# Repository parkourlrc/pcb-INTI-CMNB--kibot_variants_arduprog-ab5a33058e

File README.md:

# KiBot variants example

This is an example of how to use variants with [KiBot](https://github.com/INTI-CMNB/KiBot).

> [!TIP]
> They can be migrated to native KiCad 10 variants, here is an [example](https://inti-cmnb.github.io/kibot_variants_arduprog_native/)

## Index

* [Definition](#Definition)
* [Implementation](#Implementation)
* [Example](#Example)
* [**Results**](#Results)
  * [Schematic PDF](#Schematic-PDF)
  * [Bill of Materials](#Bill-of-Materials)
  * [PCB PDF](#PCB-PDF)
  * [Gerbers](#Gerbers)
  * [Position](#Position)
  * [3D Model](#3D-Model)
* [Changing values](#Changing-values)
* [A complete example](#A-complete-example)

# Definition

In the KiBot context a variant is what is usually known as an *assembly variant*.
So the idea is that you have **one** PCB, but various different *variants* (*flavors*) of the product.
The difference between them is which components are used.

Typical applications are:
- Optional functionality
- Support for different normatives
- Testing purposes

Currently KiBot can handle not only which components are soldered, but also different values.
The support for different values is complex and only used by a minority.
So please be patient if some use case isn't well covered, just report it.

# Implementation

To create a variant you must add specific fields to the components in the schematic.
Currently KiBot supports three methodes:

- **KiBoM style**: one field, usually named *Config*, contains information to include or exclude a component for one or more variants.
- **KiCost style**: one field assigns the component to one or more groups, you provide a regular expression to include certain groups.
- **IBoM style**: one field assigns the component to a group, you provide lists to exclude or include certain groups.

# Example

The best way to explain how to use it is using an example.
We start with an hypothetic design: the *programmer* section of the [Arduino UNO R3](https://content.arduino.cc/assets/UNO-TH_Rev3e_sch.pdf).
The schematic is the following:

This is basically an ATMega8U2 used as a bridge between USB and the Arduino UNO serial port.
So we will assume this board is useful. We'll also assume we have three possible uses:

- The full board with USB support. We'll name it **USB** variant.
- A version of the board that we want to use as a plain microcontroller. So we remove the USB. We'll name it **XTAL** variant.
- An even more modest version where we use the internal clock oscillator and we can remove the crystal. We'll name it **default** variant.

Additionally:

- In the USB version we want to remove the ICSP1 connector. We'll flash the CPU in-house and the user won't need to do it. ICPS1 will be solded for the other two variants.
- The J4 connector is completely optional. It won't be included in any variant.

The first step is to choose a variant mechanism. For this example we will use the [KiBoM](https://github.com/SchrodingersGat/KiBoM) style.
This style puts more information inside the schematic, so you need to provide less information from outside.

Now that we chose a format we must add the corresponding *tags*. We can identify four groups of components here:

- The USB components (J2, F1, R1, R2, RV1, RV2 and FB1). Used only for the **USB** variant.
- The ICSP1 connector (J5). Excluded from the **USB** variant.
- The crystal components (R3, Y1, C3, C4). Used only for the **USB** and **XTAL** variants.
- The 2x2M connector (J4). Never used.

To mark components that will be added to the board only for certain variant KiBoM uses **+VARIANT**.
And when we want to exclude a component from a variant we use **-VARIANT**.

We'll use the default *Config* field. So lets see what we'll use for each group.

- For the USB components we'll use **+USB** because these components will be used only for the **USB** variant.
- For the ICSP1 connector we'll use **-USB** because this component will be solded for all variants, except **USB**.
- Now the crystal stuff is a little bit more complex. We could use **+XTAL**, but then these components won't be included in the **USB** version.
  So what we use is **+USB,+XTAL** this makes the components available for both variants.
- The J4 case is handled in a different way. KiBoM filters removes any component mentioning the **DNF** word in the config. So we can just use it.

Now that we know what to use we'll add the *Config* field to the mentioned components.
To make it faster we can add it to one component, lets say to J4, and then use the *Tools -> Edit symbol fields* menu option.
Here is what we should have in the *Config* field:

This is all we need to add to the schematic. Now is time to configure KiBot.

If you don't know about the KiBot file format you could be interested in reading the following [explanation](https://github.com/INTI-CMNB/KiBot/blob/master/docs/KiPlotYAML.md).
YAML files are self explanatory, so perhaps you can go on even without knowing about the format.

Ok, now we have to define the three variants we mentioned before: **USB**, **XTAL** and **default**.
All variants will be put in a section named **variants**. So we'll create a list of items, each item is a variant definition.
Lets start with the simplest: **default**. Here is what we use:

```yaml
variants:
  - name: 'default'
    comment: 'Minimal PCB no USB'
    type: kibom
```

This is the section **variants** and its first item. The name is **default** and we added a comment to remmember what this variant is.
We also define the type as **kibom**, what we called *style*.

Now lets go for the second, here we add:

```yaml
  - name: 'USB'
    comment: 'Full board'
    type: kibom
    file_id: _USB
    variant: USB
```

You'll notice two new attributes: `file_id` and `variant`. The first is what we'll add to the names of the files in order to distinguish from the **default**.
And the second ... well this is just the *tag* we used to mark **USB** components.

You should be able to figure out how to define the third variant, here we go:

```yaml
  - name: 'XTAL'
    comment: 'No USB, but crystal included'
    type: kibom
    file_id: _XTAL
    variant: XTAL
```

A little bit long, but simple. Here is all together:

```yaml
variants:
  - name: 'default'
    comment: 'Minimal PCB no USB'
    type: kibom

  - name: 'USB'
    comment: 'Full board'
    type: kibom
    file_id: _USB
    variant: USB

  - name: 'XTAL'
    comment: 'No USB, but crystal included'
    type: kibom
    file_id: _XTAL
    variant: XTAL
```

This is all we need to define the variants. Of course our config file must define what to do with the variants.
But this document is about the variants, we won't focuse on the rest.
You can see the whole configuration file [here](ardu_prog.kibot.yaml).

What now? How can we tell KiBot what variant to use?
There are three methodes:

1. Use the `variant` option for an specific output.
2. Select a default variant to be used by all outputs that doesn't specify a variant.
3. Same as above but from the command line.

The simplest way is the third. In this case we just need to add `-g variant=NAME` to the command line.
Lets say we have a copy of the repo containing this example and we want to generate the BoM.
In our example the HTML BoM output is named `bom_html` so we can just run:

```bash
kibot -s run_erc,run_drc -d Result bom_html
```

This will create `Result/BoM/t1-bom.html`. To generate the BoM for the **USB** variant we can use:

```bash
kibot -s run_erc,run_drc -d USB -g variant=USB bom_html
```

And we'll get a different BoM in `USB/BoM/t1-bom_USB.html`.

The CI/CD workflow for this repo runs the ERC and DRC checks and then generates all the configured outputs for the three variants.
The commands used are approximately these:

```bash
kibot -d Generated -s run_drc -i
kibot -d Generated -s run_erc -i
kibot -d Generated/default -g variant=default -s run_erc,run_drc
kibot -d Generated/USB -g variant=USB -s run_erc,run_drc
kibot -d Generated/XTAL -g variant=XTAL -s run_erc,run_drc
```

The first two are the checks, no output generated. The other three skips the checks and generates all outputs for each variant.
All files are stored in the `Generated` folder.

# Results

Here is what we get, you can download the results obtained on GitHub CI/CD Actions from [here](https://github.com/INTI-CMNB/kibot_variants_arduprog/actions/runs/4584580459).
Click on the images to get a larger image or the generated document.

## Schematic PDF

Excluded components are marked with a cross:

- Default variant

- XTAL variant

- USB variant

## Bill of Materials

Excluded components are listed as DNF in a separated list. Note we could also remove them.

- Default variant

- XTAL variant

- USB variant

The XLSX files contain the same information, arranged a little bit different, here is the USB variant:

## PCB PDF

Excluded components are marked with a cross in the *.Fab layer. Their solder paste and adhesive glue is removed from *.Paste and *.Adhes.
The following PDFs were gnerated including F.Fab, F.Paste, F.Adhes and Dwgs.User:

- Default variant

- XTAL variant

- USB variant

## Gerbers

Excluded components are marked with a cross in the *.Fab layer. Their solder paste and adhesive glue is removed from *.Paste and *.Adhes:

- Default variant

- XTAL variant

- USB variant

## Position

Here only the fitted components are included in the pick and place file:

- Default variant
```
### Module positions - created on Thu 10 Sep 2020 20:10:57  ###
### Printed by KiBot
## Unit = mm, Angle = deg.
## Side : both
# Ref   Val                  Package                                     PosX       PosY       Rot        Side
C1     47uF                 CP_Elec_8x10                                130.8354   -94.8944   270.0000   top
C2     100nF                C_0805_2012Metric                           123.0000   -90.9000   0.0000     top
C5     1uF                  C_0805_2012Metric                           163.3220   -89.1540   270.0000   top
C6     100nF                C_0805_2012Metric                           162.3822   -82.0674   90.0000    top
C7     100nF                C_0805_2012Metric                           153.9748   -78.8670   0.0000     top
C8     100nF                C_0805_2012Metric                           144.7546   -78.9686   90.0000    top
D1     CD1206-S01575        D_1206_3216Metric                           162.8140   -96.7740   90.0000    top
D2     LED                  LED_0805_2012Metric                         147.3200   -74.9500   90.0000    top
D3     LED                  LED_0805_2012Metric                         144.7800   -74.9500   90.0000    top
J1     Barrel_Jack_Switch   BarrelJack_CLIFF_FC681465S_SMT_Horizontal   126.1000   -81.2000   0.0000     top
R4     10K                  R_0805_2012Metric                           159.0040   -95.7580   90.0000    top
R5     1K                   R_0805_2012Metric                           144.7546   -82.8040   270.0000   top
R6     1K                   R_0805_2012Metric                           147.3200   -70.1748   270.0000   top
R7     1K                   R_0805_2012Metric                           144.7800   -70.1748   270.0000   top
U1     ATmega8U2-AU         TQFP-32_7x7mm_P0.8mm                        154.4320   -85.8520   270.0000   top
## End
```
- XTAL variant
```
### Module positions - created on Thu 10 Sep 2020 20:11:59  ###
### Printed by KiBot
## Unit = mm, Angle = deg.
## Side : both
# Ref   Val                  Package                                     PosX       PosY       Rot        Side
C1     47uF                 CP_Elec_8x10                                130.8354   -94.8944   270.0000   top
C2     100nF                C_0805_2012Metric                           123.0000   -90.9000   0.0000     top
C3     22pF                 C_0805_2012Metric                           162.2600   -75.1160   270.0000   top
C4     22pF                 C_0805_2012Metric                           155.9100   -75.1160   270.0000   top
C5     1uF                  C_0805_2012Metric                           163.3220   -89.1540   270.0000   top
C6     100nF                C_0805_2012Metric                           162.3822   -82.0674   90.0000    top
C7     100nF                C_0805_2012Metric                           153.9748   -78.8670   0.0000     top
C8     100nF                C_0805_2012Metric                           144.7546   -78.9686   90.0000    top
D1     CD1206-S01575        D_1206_3216Metric                           162.8140   -96.7740   90.0000    top
D2     LED                  LED_0805_2012Metric                         147.3200   -74.9500   90.0000    top
D3     LED                  LED_0805_2012Metric                         144.7800   -74.9500   90.0000    top
J1     Barrel_Jack_Switch   BarrelJack_CLIFF_FC681465S_SMT_Horizontal   126.1000   -81.2000   0.0000     top
R3     1M                   R_0805_2012Metric                           158.9580   -75.8780   180.0000   top
R4     10K                  R_0805_2012Metric                           159.0040   -95.7580   90.0000    top
R5     1K                   R_0805_2012Metric                           144.7546   -82.8040   270.0000   top
R6     1K                   R_0805_2012Metric                           147.3200   -70.1748   270.0000   top
R7     1K                   R_0805_2012Metric                           144.7800   -70.1748   270.0000   top
U1     ATmega8U2-AU         TQFP-32_7x7mm_P0.8mm                        154.4320   -85.8520   270.0000   top
Y1     16MHz                Crystal_SMD_Abracon_ABM3-2Pin_5.0x3.2mm     158.9278   -70.0278   180.0000   top
## End
```
- USB variant
```
### Module positions - created on Thu 10 Sep 2020 20:11:27  ###
### Printed by KiBot
## Unit = mm, Angle = deg.
## Side : both
# Ref   Val                  Package                                     PosX       PosY       Rot        Side
C1      47uF                 CP_Elec_8x10                                130.8354   -94.8944   270.0000   top
C2      100nF                C_0805_2012Metric                           123.0000   -90.9000   0.0000     top
C3      22pF                 C_0805_2012Metric                           162.2600   -75.1160   270.0000   top
C4      22pF                 C_0805_2012Metric                           155.9100   -75.1160   270.0000   top
C5      1uF                  C_0805_2012Metric                           163.3220   -89.1540   270.0000   top
C6      100nF                C_0805_2012Metric                           162.3822   -82.0674   90.0000    top
C7      100nF                C_0805_2012Metric                           153.9748   -78.8670   0.0000     top
C8      100nF                C_0805_2012Metric                           144.7546   -78.9686   90.0000    top
D1      CD1206-S01575        D_1206_3216Metric                           162.8140   -96.7740   90.0000    top
D2      LED                  LED_0805_2012Metric                         147.3200   -74.9500   90.0000    top
D3      LED                  LED_0805_2012Metric                         144.7800   -74.9500   90.0000    top
F1      MF-MSMF050-2         R_1812_4532Metric                           167.8940   -77.2160   0.0000     top
FB1     BLM21PG221SN1D       R_0805_2012Metric                           167.8940   -90.6780   180.0000   top
J1      Barrel_Jack_Switch   BarrelJack_CLIFF_FC681465S_SMT_Horizontal   126.1000   -81.2000   0.0000     top
R1      22R                  R_0805_2012Metric                           166.3700   -86.1060   0.0000     top
R2      22R                  R_0805_2012Metric                           166.3700   -83.8200   0.0000     top
R3      1M                   R_0805_2012Metric                           158.9580   -75.8780   180.0000   top
R4      10K                  R_0805_2012Metric                           159.0040   -95.7580   90.0000    top
R5      1K                   R_0805_2012Metric                           144.7546   -82.8040   270.0000   top
R6      1K                   R_0805_2012Metric                           147.3200   -70.1748   270.0000   top
R7      1K                   R_0805_2012Metric                           144.7800   -70.1748   270.0000   top
RV1     CG0603MLC-05E        R_0603_1608Metric                           170.4340   -87.3505   270.0000   top
RV2     CG0603MLC-05E        R_0603_1608Metric                           170.4340   -82.3214   90.0000    top
U1      ATmega8U2-AU         TQFP-32_7x7mm_P0.8mm                        154.4320   -85.8520   270.0000   top
Y1      16MHz                Crystal_SMD_Abracon_ABM3-2Pin_5.0x3.2mm     158.9278   -70.0278   180.0000   top
## End
```

## 3D Model

Excluded components are removed from the 3D model (STEP file, 3D Viewer render and Blender export):

- Default variant (click to enlarge)

- XTAL variant (click to enlarge)

- USB variant (click to enlarge)

# Changing values

Variants can also affect any of the component fields. In order to overwrite one field value when a variant is selected you must define a field named `VARIANT:FIELD`.
The value for this field will replace the value of the regular `FIELD` when the `VARIANT` is in use.

Here is an example, if you have a resistor with a value of 1k and you want this value to change to 2k2 when the `test` variant is in use you just need to define a field named `test:value` and assign `2k2` to this field.

To enable it you just need to add a `pre_transform` filter of the type `var_rename` to the variant performing the transformation. Suppose you have the following variants:

```yaml
variants:
  - name: 'production'
    comment: 'Production variant'
    type: kibom
    file_id: '_(PROD)'
    variant: PROD

  - name: 'development'
    comment: 'Development variant'
    type: kibom
    file_id: '_(DEV)'
    variant: DEV
```

And you want to both apply such a transformation you can define:

```yaml
filters:
  - name: 'Variant rename'
    type: var_rename
    separator: ':'
    variant_to_value: true

variants:
  - name: 'production'
    comment: 'Production variant'
    type: kibom
    file_id: '_(PROD)'
    variant: PROD
    pre_transform: 'Variant rename'

  - name: 'development'
    comment: 'Development variant'
    type: kibom
    file_id: '_(DEV)'
    variant: DEV
    pre_transform: 'Variant rename'
```

The `separator` option controls which character is used to separate the `VARIANT` and the `FIELD` in the field name.

The `variant_to_value` enables the conversion from fields named `VARIANT` to the component value when the variant is in use.

To make things simpler you can use an internally defined filter called `_var_rename`. This is a `var_rename` filter with `:` as separator and `variant_to_value` disabled. Using it the configuration is simpler:

```yaml
variants:
  - name: 'production'
    comment: 'Production variant'
    type: kibom
    file_id: '_(PROD)'
    variant: PROD
    pre_transform: '_var_rename'

  - name: 'development'
    comment: 'Development variant'
    type: kibom
    file_id: '_(DEV)'
    variant: DEV
    pre_transform: '_var_rename'
```

# A complete example

The configuration file used in this example can be found [here](https://github.com/INTI-CMNB/kibot_variants_arduprog/blob/master/ardu_prog.kibot.yaml).

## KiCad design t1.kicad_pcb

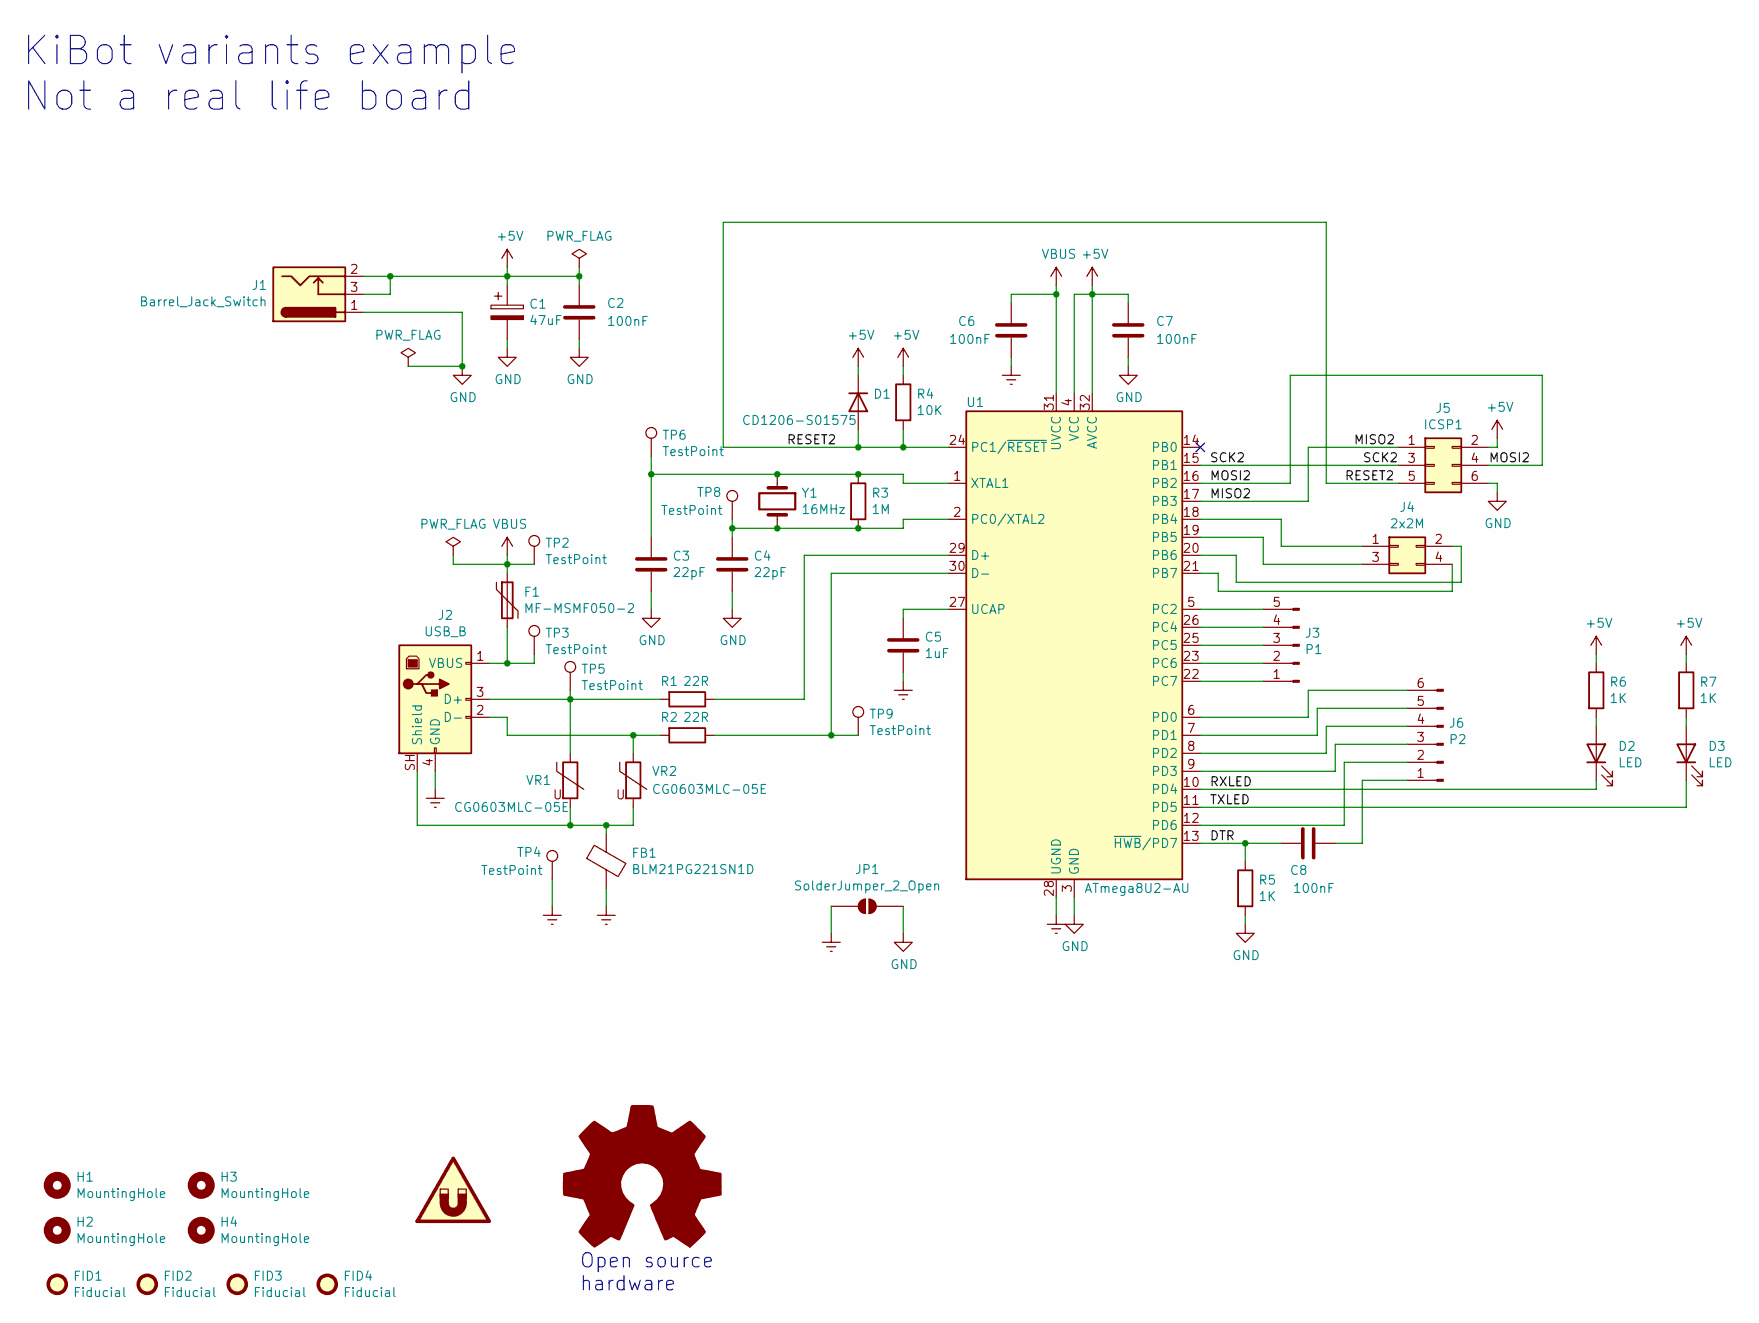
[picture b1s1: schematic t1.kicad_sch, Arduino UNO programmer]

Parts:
C1: 47uF; CP_Elec_8x10
C2, C6, C7, C8: 100nF; C_0805_2012Metric
C3, C4: 22pF; C_0805_2012Metric
C5: 1uF; C_0805_2012Metric
D1: CD1206-S01575; D_1206_3216Metric
D2, D3: LED; LED_0805_2012Metric
F1: MF-MSMF050-2; R_1812_4532Metric
FB1: BLM21PG221SN1D; R_0805_2012Metric
FID1, FID2, FID3, FID4: Fiducial; Fiducial_0.75mm_Mask1.5mm
H1, H2, H3, H4: MountingHole; MountingHole_2.7mm_M2.5
J1: Barrel_Jack_Switch; BarrelJack_CLIFF_FC681465S_SMT_Horizontal
J2: USB_B; USB_B_Lumberg_2411_02_Horizontal
J3: P1; PinHeader_1x05_P2.54mm_Vertical
J4: 2x2M; PinHeader_2x02_P2.54mm_Vertical
J5: ICSP1; PinHeader_2x03_P2.54mm_Vertical
J6: P2; PinHeader_1x06_P2.54mm_Vertical
JP1: SolderJumper_2_Open; SolderJumper-2_P1.3mm_Open_RoundedPad1.0x1.5mm
LOGO1: Logo_Open_Hardware_Large; OSHW-Logo_11.4x12mm_SilkScreen
R1, R2: 22R; R_0805_2012Metric
R3: 1M; R_0805_2012Metric
R4: 10K; R_0805_2012Metric
R5, R6, R7: 1K; R_0805_2012Metric
SYM1: SYM_Magnet_Large
TP2, TP3, TP4, TP5, TP6, TP8, TP9: TestPoint; TestPoint_Pad_D1.0mm
U1: ATmega8U2-AU; TQFP-32_7x7mm_P0.8mm
VR1, VR2: CG0603MLC-05E; R_0603_1608Metric
Y1: 16MHz; Crystal_SMD_Abracon_ABM3-2Pin_5.0x3.2mm

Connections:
+5V: C1.1, C2.1, C7.1, D1.1 (K), J1.2, J1.3, J5.2, R4.1, R6.1, R7.1, U1.4 (VCC), U1.32 (AVCC)
/DTR: C8.1, R5.1, U1.13 (~HWB/PD7)
/MISO2: J5.1, U1.17 (PB3)
/MOSI2: J5.4, U1.16 (PB2)
/RESET2: D1.2 (A), J5.5, R4.2, U1.24 (PC1/~RESET)
/RXLED: D2.1 (K), U1.10 (PD4)
/SCK2: J5.3, U1.15 (PB1)
/TXLED: D3.1 (K), U1.11 (PD5)
Earth: C5.2, C6.2, FB1.2, J2.4 (GND), JP1.1 (A), TP4.1 (1_1), U1.28 (UGND)
GND: C1.2, C2.2, C3.2, C4.2, C7.2, J1.1, J5.6, JP1.2 (B), R5.2, U1.3 (GND)
unnamed: D2.2 (A), R6.2
unnamed: D3.2 (A), R7.2
unnamed: J2.3 (D+), R1.2, TP5.1 (1_1), VR1.1
unnamed: J2.2 (D-), R2.2, VR2.1
unnamed: FB1.1, J2.SH (Shield), VR1.2, VR2.2
unnamed: F1.2, J2.1 (VBUS), TP3.1 (1_1)
unnamed: J3.1, U1.22 (PC7)
unnamed: J3.2, U1.23 (PC6)
unnamed: J3.3, U1.25 (PC5)
unnamed: J3.4, U1.26 (PC4)
unnamed: J3.5, U1.5 (PC2)
unnamed: J4.1, U1.18 (PB4)
unnamed: J4.2, U1.20 (PB6)
unnamed: J4.3, U1.19 (PB5)
unnamed: J4.4, U1.21 (PB7)
unnamed: C8.2, J6.1
unnamed: J6.2, U1.12 (PD6)
unnamed: J6.3, U1.9 (PD3)
unnamed: J6.4, U1.8 (PD2)
unnamed: J6.5, U1.7 (PD1)
unnamed: J6.6, U1.6 (PD0)
unnamed: R1.1, U1.29 (D+)
unnamed: R2.1, TP9.1 (1_1), U1.30 (D-)
unnamed: C4.1, R3.2, TP8.1 (1_1), U1.2 (PC0/XTAL2), Y1.2
unnamed: C5.1, U1.27 (UCAP)
unnamed: C3.1, R3.1, TP6.1 (1_1), U1.1 (XTAL1), Y1.1
VBUS: C6.1, F1.1, TP2.1 (1_1), U1.31 (UVCC)

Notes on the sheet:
Open source hardware
KiBot variants example Not a real life board

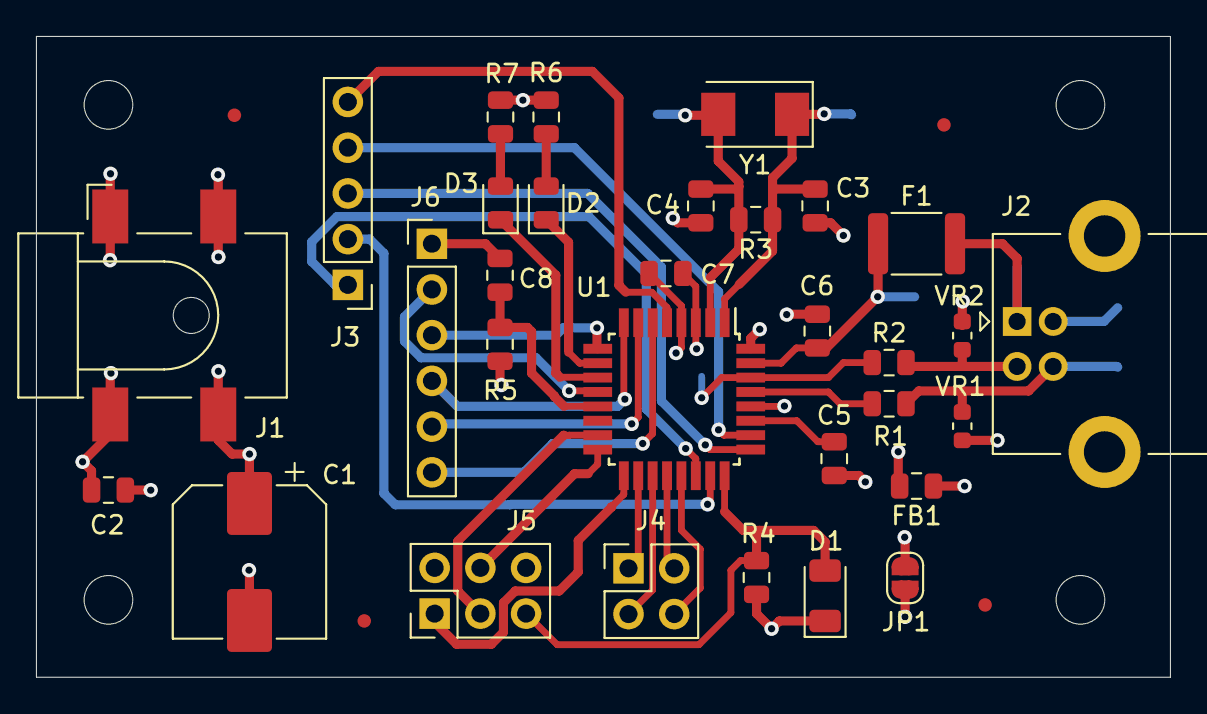
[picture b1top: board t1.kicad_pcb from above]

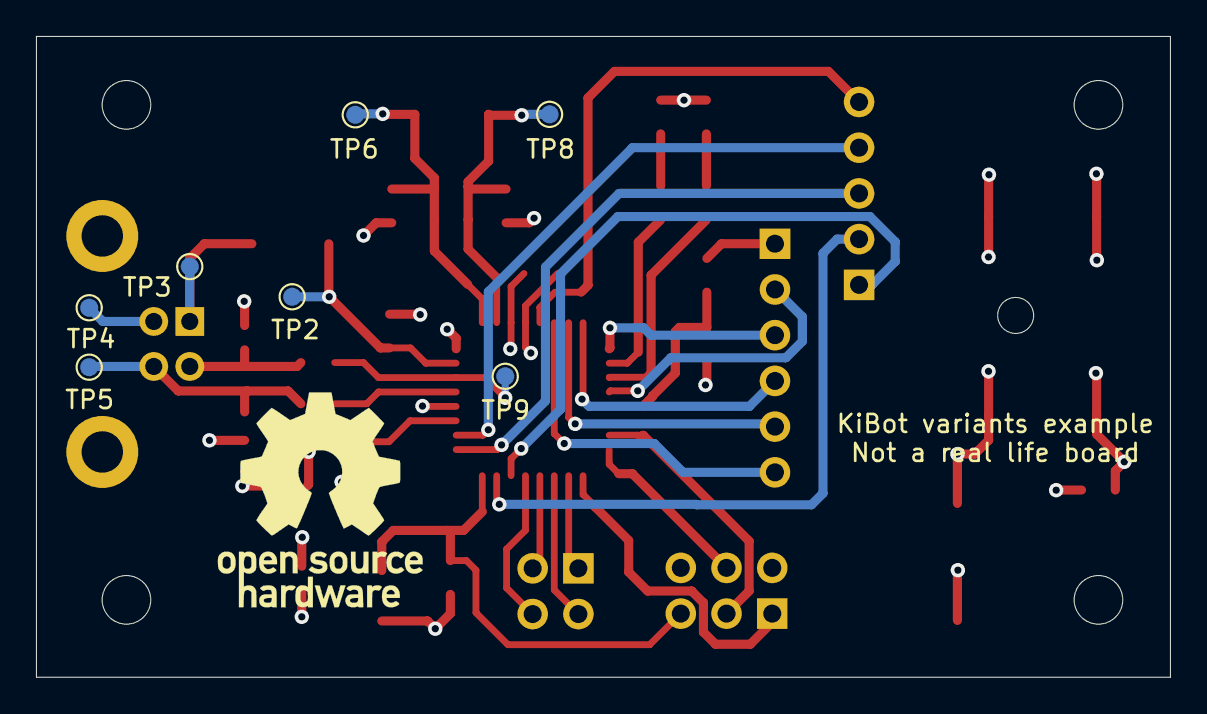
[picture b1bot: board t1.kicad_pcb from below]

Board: 4 copper layers, 63.0 x 35.6 mm, 47 parts (8 on the bottom side), 37 nets.

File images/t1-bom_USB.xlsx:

|  | KiBot variants example
 |  | Schematic: | t1 | Component Groups: | 21
 |  | Variant: | USB | Component Count: | 30
 |  | Revision: | Git:8c4e343 | Fitted Components: | 28
 |  | Date: | 2026-07-15T12:20+00:00 | Number of PCBs: | 1
 |  | KiCad Version: | 10.0.4-10.0.4~ubuntu25.10.1 | Total Components: | 28
Row | References | Quantity Per PCB | Value | Manufacturer | Manf. Part | Footprint
1 | C3 C4 | 2 | 22 pF |  |  | C_0805_2012Metric
2 | C2 C6 C7 C8 | 4 | 100 nF |  |  | C_0805_2012Metric
3 | C5 | 1 | 1 µF |  |  | C_0805_2012Metric
4 | C1 | 1 | 47 µF | Vishay Beyschlag/Draloric/BC Components | MAL215371479E3 | CP_Elec_8x10
5 | D1 | 1 | CD1206-S01575 |  |  | D_1206_3216Metric
6 | D2 D3 | 2 | LED | OSRAM Opto Semiconductors Inc. | LG R971-KN-1 | LED_0805_2012Metric
7 | F1 | 1 | MF-MSMF050-2 |  |  | R_1812_4532Metric
8 | FB1 | 1 | BLM21PG221SN1D | Murata | BLM21PG221SN1D | R_0805_2012Metric
9 | J1 | 1 | Barrel_Jack_Switch | Würth Elektronik | 694106106102 | BarrelJack_CLIFF_FC681465S_SMT_Horizontal
10 | J3 | 1 | P1 |  |  | PinHeader_1x05_P2.54mm_Vertical
11 | J6 | 1 | P2 |  |  | PinHeader_1x06_P2.54mm_Vertical
12 | J2 | 1 | USB_B | TE Connectivity AMP Connectors | 292304-1 | USB_B_Lumberg_2411_02_Horizontal
13 | R1 R2 | 2 | 22 Ω |  |  | R_0805_2012Metric
14 | R5 R6 R7 | 3 | 1 kΩ |  |  | R_0805_2012Metric
15 | R4 | 1 | 10 kΩ |  |  | R_0805_2012Metric
16 | R3 | 1 | 1 MΩ |  |  | R_0805_2012Metric
17 | U1 | 1 | ATmega8U2-AU |  |  | TQFP-32_7x7mm_P0.8mm
18 | VR1 VR2 | 2 | CG0603MLC-05E | Bourns Inc. | CG0603MLC-05E | R_0603_1608Metric
19 | Y1 | 1 | 16MHz | Abracon LLC | ABM3-16.000MHZ-B2-T | Crystal_SMD_Abracon_ABM3-2Pin_5.0x3.2mm
